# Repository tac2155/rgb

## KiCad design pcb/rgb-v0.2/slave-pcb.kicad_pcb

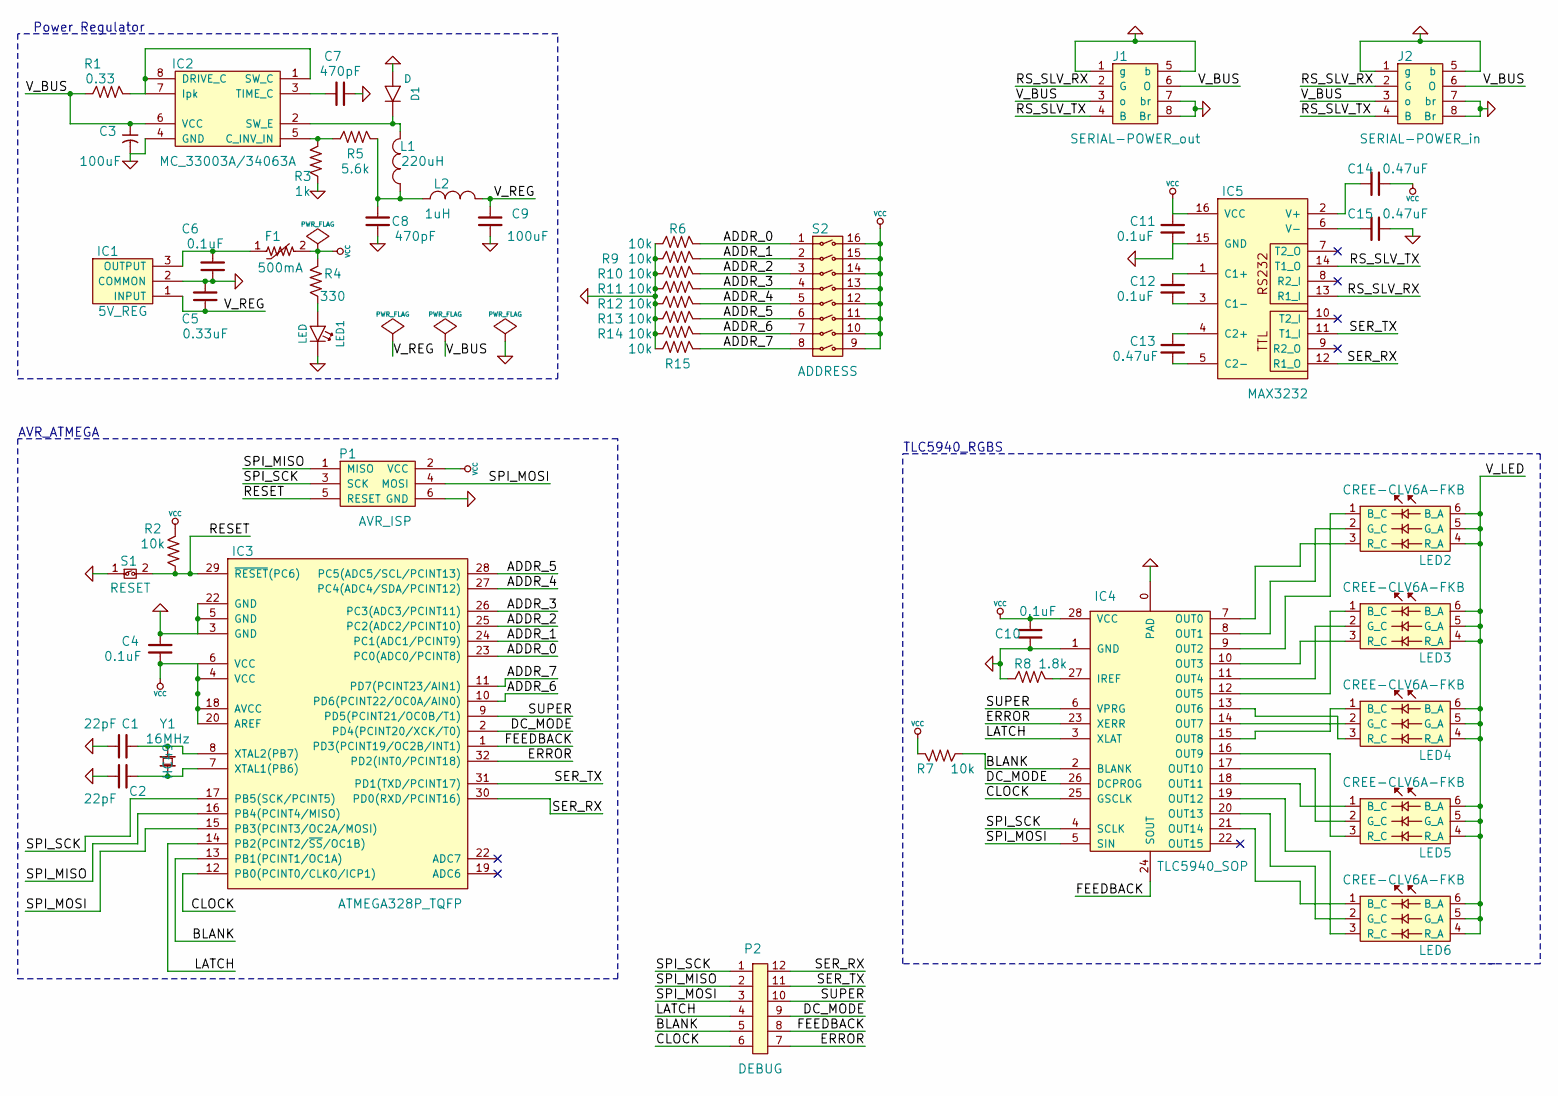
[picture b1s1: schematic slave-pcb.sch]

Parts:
C1, C2: 22pF; 0603(1608m)
C3, C9: 100uF
C4, C10, C11, C12: 0.1uF; 0603(1608m)
C5: 0.33uF
C6: 0.1uF
C7, C8: 470pF
C13, C14, C15: 0.47uF; 0603(1608m)
D1: D
F1: 500mA
IC1: 5V_REG
IC2: MC_33003A/34063A
IC3: ATMEGA328P_TQFP; TQFP32_7mm
IC4: TLC5940_SOP; HTSSOP28
IC5: MAX3232; TSSOP16
J1: SERIAL-POWER_out; 8P8C_thru
J2: SERIAL-POWER_in; 8P8C_thru
L1: 220uH
L2: 1uH
LED1: LED
LED2, LED3, LED4, LED5, LED6: CREE-CLV6A-FKB; PLCC6
P1: AVR_ISP; 2x3-array
P2: DEBUG; SIP12
R1: 0.33
R2, R7: 10k; 0603(1608m)
R3: 1k
R4: 330
R5: 5.6k
R6, R9, R10, R11, R12, R13, R14, R15: 10k
R8: 1.8k; 0603(1608m)
S1: RESET; SPST_4-pin-thru
S2: ADDRESS; DIP16
Y1: 16MHz; HC49

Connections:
/ADDR_0: IC3.23 (PC0(ADC0/PCINT8)), R6.2, S2.1
/ADDR_1: IC3.24 (PC1(ADC1/PCINT9)), R9.2, S2.2
/ADDR_2: IC3.25 (PC2(ADC2/PCINT10)), R10.2, S2.3
/ADDR_3: IC3.26 (PC3(ADC3/PCINT11)), R11.2, S2.4
/ADDR_4: IC3.27 (PC4(ADC4/SDA/PCINT12)), R12.2, S2.5
/ADDR_5: IC3.28 (PC5(ADC5/SCL/PCINT13)), R13.2, S2.6
/ADDR_6: IC3.10 (PD6(PCINT22/OC0A/AIN0)), R14.2, S2.7
/ADDR_7: IC3.11 (PD7(PCINT23/AIN1)), R15.2, S2.8
/BLANK: IC3.13 (PB1(PCINT1/OC1A)), IC4.2 (BLANK), P2.5, R7.1
/CLOCK: IC3.12 (PB0(PCINT0/CLKO/ICP1)), IC4.25 (GSCLK), P2.6
/DC_MODE: IC3.2 (PD4(PCINT20/XCK/T0)), IC4.26 (DCPROG), P2.9
/ERROR: IC3.32 (PD2(INT0/PCINT18)), IC4.23 (XERR), P2.7
/FEEDBACK: IC3.1 (PD3(PCINT19/OC2B/INT1)), IC4.24 (SOUT), P2.8
/LATCH: IC3.14 (PB2(PCINT2/~SS~/OC1B)), IC4.3 (XLAT), P2.4
/RESET: IC3.29 (~RESET~(PC6)), P1.5 (RESET), R2.1, S1.2
/RS_SLV_RX: IC5.13 (R1_I), J1.2 (G), J2.2 (G)
/RS_SLV_TX: IC5.14 (T1_O), J1.4 (B), J2.4 (B)
/SER_RX: IC3.30 (PD0(RXD/PCINT16)), IC5.12 (R1_O), P2.12
/SER_TX: IC3.31 (PD1(TXD/PCINT17)), IC5.11 (T1_I), P2.11
/SPI_MISO: IC3.16 (PB4(PCINT4/MISO)), P1.1 (MISO), P2.2
/SPI_MOSI: IC3.15 (PB3(PCINT3/OC2A/MOSI)), IC4.5 (SIN), P1.4 (MOSI), P2.3
/SPI_SCK: IC3.17 (PB5(SCK/PCINT5)), IC4.4 (SCLK), P1.3 (SCK), P2.1
/SUPER: IC3.9 (PD5(PCINT21/OC0B/T1)), IC4.6 (VPRG), P2.10
/V_BUS: C3.1, IC2.6 (VCC), J1.3 (o), J1.6 (O), J2.3 (o), J2.6 (O), R1.1
/V_LED: LED2.4 (R_A), LED2.5 (G_A), LED2.6 (B_A), LED3.4 (R_A), LED3.5 (G_A), LED3.6 (B_A), LED4.4 (R_A), LED4.5 (G_A), LED4.6 (B_A), LED5.4 (R_A), LED5.5 (G_A), LED5.6 (B_A), LED6.4 (R_A), LED6.5 (G_A), LED6.6 (B_A)
/V_REG: C5.1, C9.2, IC1.1 (INPUT), L2.2
GND: C1.1, C2.1, C3.2, C4.2, C5.2, C6.1, C7.2, C8.1, C9.1, C10.2, C11.1, C15.2, D1.2 (A), IC1.2 (COMMON), IC2.4 (GND), IC3.3 (GND), IC3.5 (GND), IC3.22 (ADC7), IC4.0 (PAD), IC4.1 (GND), IC5.15 (GND), J1.1 (g), J1.5 (b), J1.7 (br), J1.8 (Br), J2.1 (g), J2.5 (b), J2.7 (br), J2.8 (Br), LED1.2 (K), P1.6 (GND), R3.1, R6.1, R8.1, R9.1, R10.1, R11.1, R12.1, R13.1, R14.1, R15.1, S1.1
unnamed: IC4.27 (IREF), R8.2
unnamed: C12.1, IC5.3 (C1-)
unnamed: C13.2, IC5.5 (C2-)
unnamed: C15.1, IC5.6 (V-)
unnamed: IC4.21 (OUT14), LED6.1 (B_C)
unnamed: IC4.16 (OUT9), LED5.3 (R_C)
unnamed: IC4.18 (OUT11), LED5.1 (B_C)
unnamed: IC4.20 (OUT13), LED6.2 (G_C)
unnamed: IC4.14 (OUT7), LED4.2 (G_C)
unnamed: IC4.12 (OUT5), LED3.1 (B_C)
unnamed: IC4.17 (OUT10), LED5.2 (G_C)
unnamed: IC4.8 (OUT1), LED2.2 (G_C)
unnamed: IC4.10 (OUT3), LED3.3 (R_C)
unnamed: IC4.9 (OUT2), LED2.1 (B_C)
unnamed: IC4.11 (OUT4), LED3.2 (G_C)
unnamed: C6.2, F1.1, IC1.3 (OUTPUT)
unnamed: LED1.1 (A), R4.1
unnamed: IC4.19 (OUT12), LED6.3 (R_C)
unnamed: IC4.13 (OUT6), LED4.3 (R_C)
unnamed: IC4.15 (OUT8), LED4.1 (B_C)
unnamed: IC4.7 (OUT0), LED2.3 (R_C)
unnamed: D1.1 (C), IC2.2 (SW_E), L1.2
unnamed: C8.2, L1.1, L2.1, R5.2
unnamed: IC2.1 (SW_C), IC2.7 (Ipk), IC2.8 (DRIVE_C), R1.2
unnamed: C7.1, IC2.3 (TIME_C)
unnamed: IC2.5 (C_INV_IN), R3.2, R5.1
unnamed: C12.2, IC5.1 (C1+)
unnamed: C14.1, IC5.2 (V+)
unnamed: C13.1, IC5.4 (C2+)
unnamed: C1.2, IC3.8 (XTAL2(PB7)), Y1.1
unnamed: C2.2, IC3.7 (XTAL1(PB6)), Y1.2
VCC: C4.1, C10.1, C11.2, C14.2, F1.2, IC3.4 (VCC), IC3.6 (VCC), IC3.18 (AVCC), IC3.20 (AREF), IC4.28 (VCC), IC5.16 (VCC), P1.2 (VCC), R2.2, R4.2, R7.2, S2.9, S2.10, S2.11, S2.12, S2.13, S2.14, S2.15, S2.16

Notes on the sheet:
Power Regulator
AVR_ATMEGA
TLC5940_RGBS

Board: 2 copper layers, 52 parts (0 on the bottom side), 59 nets, no tracks yet.

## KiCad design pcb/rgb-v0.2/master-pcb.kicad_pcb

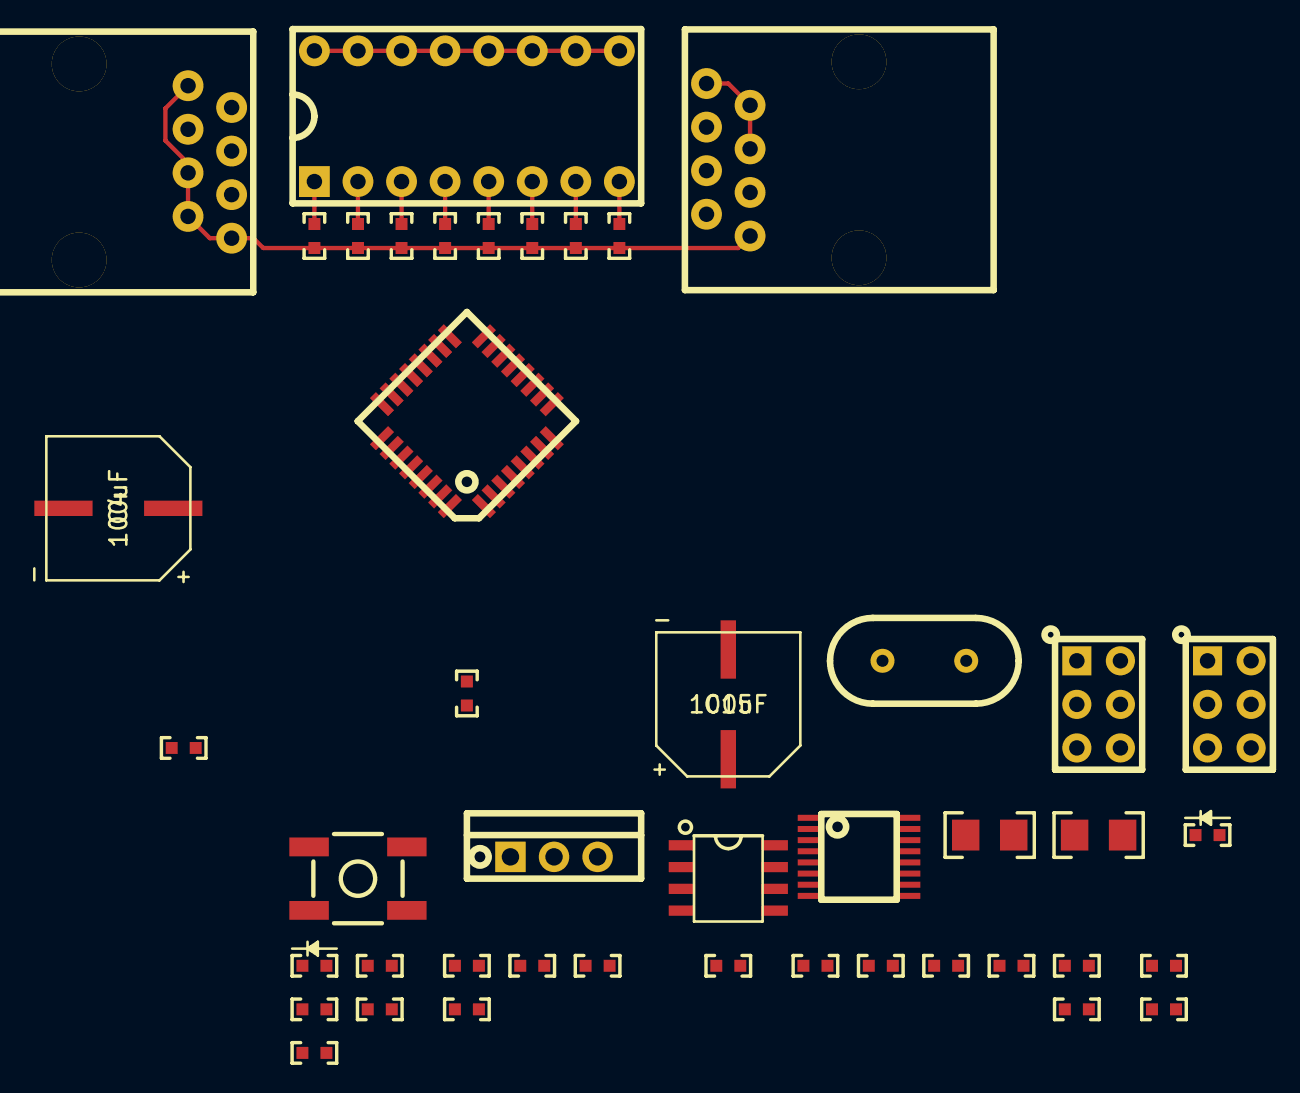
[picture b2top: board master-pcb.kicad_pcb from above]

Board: 2 copper layers, 44 parts (0 on the bottom side), 35 nets.

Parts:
C1, C2: 22pF; 0603(1608m)
C3, C6, C9, C10, C11: 0.1uF; 0603(1608m)
C4, C15: 100uF; CYLIN_CAP
C5: 0.33uF; 0603(1608m)
C7, C8: 470pF; 0603(1608m)
C12, C13: 0.47uF; 0603(1608m)
C14: 10uF; 1206(3216m)
D1: D; 0603(1608m)_LED
F1: 500mA; 1206(3216m)
IC1: 5V_REG; TO220_3pin
IC2: MC_33003A/34063A; SOIC8
IC3: ATMEGA328P_TQFP; TQFP32_7mm
IC4: MAX3232; TSSOP16
J1: SERIAL_POWER_OUT_L; 8P8C_thru
J2: SERIAL_POWER_OUT_R; 8P8C_thru
L1: 220uH; 0603(1608m)
L2: 1uH; 0603(1608m)
LED1: LED; 0603(1608m)_LED
P1: AVR_ISP; 2x3-array
PW1: DC_BARREL_JACK; 2x3-array
R1, R6, R7, R8, R9, R10, R11, R12, R13: 10k; 0603(1608m)
R2: 0.33; 0603(1608m)
R3: 330; 0603(1608m)
R4: 1k; 0603(1608m)
R5: 5.6k; 0603(1608m)
S1: RESET; SPST_4-pin-sm
S2: ADDRESS; DIP16
Y1: 16MHz; HC49

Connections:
/ADDR_0: IC3.23, R6.2, S2.1
/ADDR_1: IC3.24, R7.2, S2.2
/ADDR_2: IC3.25, R8.2, S2.3
/ADDR_3: IC3.26, R9.2, S2.4
/ADDR_4: IC3.27, R10.2, S2.5
/ADDR_5: IC3.28, R11.2, S2.6
/ADDR_6: IC3.10, R12.2, S2.7
/ADDR_7: IC3.11, R13.2, S2.8
/MISO: IC3.16, P1.1
/MOSI: IC3.15, P1.4
/RESET: IC3.29, P1.5, R1.2, S1.2
/RS_SLV_RX: IC4.13, J1.4, J2.4
/RS_SLV_TX: IC4.14, J1.2, J2.2
/SCK: IC3.17, P1.3
/SERIAL_RX: IC3.30, IC4.12
/SERIAL_TX: IC3.31, IC4.11
/V_BUS: C4.1, C14.2, IC2.6, J1.3, J1.6, J2.3, J2.6, PW1.3, R2.1
/V_REG: C5.1, C15.2, IC1.1, L2.2
GND: C1.1, C2.1, C3.1, C4.2, C5.2, C6.1, C7.2, C8.1, C9.1, C13.2, C14.1, C15.1, D1.2, IC1.2, IC2.4, IC3.3, IC3.5, IC3.21, IC4.15, J1.1, J1.5, J1.7, J1.8, J2.1, J2.5, J2.7, J2.8, LED1.2, P1.6, PW1.1, PW1.2, R4.1, R6.1, R7.1, R8.1, R9.1, R10.1, R11.1, R12.1, R13.1, S1.1
unnamed: C7.1, IC2.3
unnamed: C8.2, L1.1, L2.1, R5.2
unnamed: D1.1, IC2.2, L1.2
unnamed: IC2.5, R4.2, R5.1
unnamed: C12.1, IC4.2
unnamed: C13.1, IC4.6
unnamed: C10.2, IC4.1
unnamed: C10.1, IC4.3
unnamed: C11.1, IC4.5
unnamed: C11.2, IC4.4
unnamed: LED1.1, R3.1
unnamed: C6.2, F1.1, IC1.3
unnamed: C1.2, IC3.8, Y1.2
unnamed: C2.2, IC3.7, Y1.1
unnamed: IC2.1, IC2.7, IC2.8, R2.2
VCC: C3.2, C9.2, C12.2, F1.2, IC3.4, IC3.6, IC3.18, IC3.20, IC4.16, P1.2, R1.1, R3.2, S2.9, S2.10, S2.11, S2.12, S2.13, S2.14, S2.15, S2.16

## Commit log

2013-06-13 added bouncing color effect
2013-06-13 attempting all fade
2013-06-13 all fade working
2013-06-13 minor changes
2013-06-13 added waterfall effect
2013-06-13 added outline for checkFlag()
2013-06-13 double waterfall
2013-06-14 serial working
2013-06-14 added address recognition (sort of)
2013-06-14 basic serial send
2013-06-14 added basic color effects
2013-06-14 call and response
2013-06-14 added white effect
2013-06-18 seperated USART into own file
2013-06-19 giving up on serial for now
2013-06-19 created master board schematic
2013-06-19 working on footprint
2013-06-19 footnote
2013-07-18 still modifying
2013-07-18 UART working! (i think)
2013-07-18 cycle through all effects with UART interrupts
2013-07-18 uart success
